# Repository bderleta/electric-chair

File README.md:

# Electric Chair

AVR Parallel Programmer

## Overview

This is an application of AVRxDB32 MCU with MCP2221A USB-UART/USB-I2C interface chip, implementing parallel programming protocol for ATmega32 and 
other MCUs with similar programming interface. 12V programming voltage is generated onboard by MAX632-based converter.

Firmware stub for AVR128DB32 is available at https://github.com/bderleta/electric-chair-firmware, probably it can be built for other chips from
AVRxDB32 family. The MCP2221A is running at its stock settings and no reconfiguration is necessary, though adjustment of power requirement limit is 
recommended.

## Known flaws of first revision
- Significant USB inrush current (can be adjusted by lowering C2 value, but...)
- Converter input ripple of about 100mV (still testing)
- "12V" and "HVRST" leds are consuming majority of converter's output :)

## Changes coming in second revision

- MAX662-based converter
- XTAL1 line connected to dedicated waveform output of AVR
- PROGRAM button connected to the CCL input in order to enable debouncing using CCL filters
- Elimination of 20-pin socket, instead DIP-40 and DIP-28 ZIF sockets will be placed

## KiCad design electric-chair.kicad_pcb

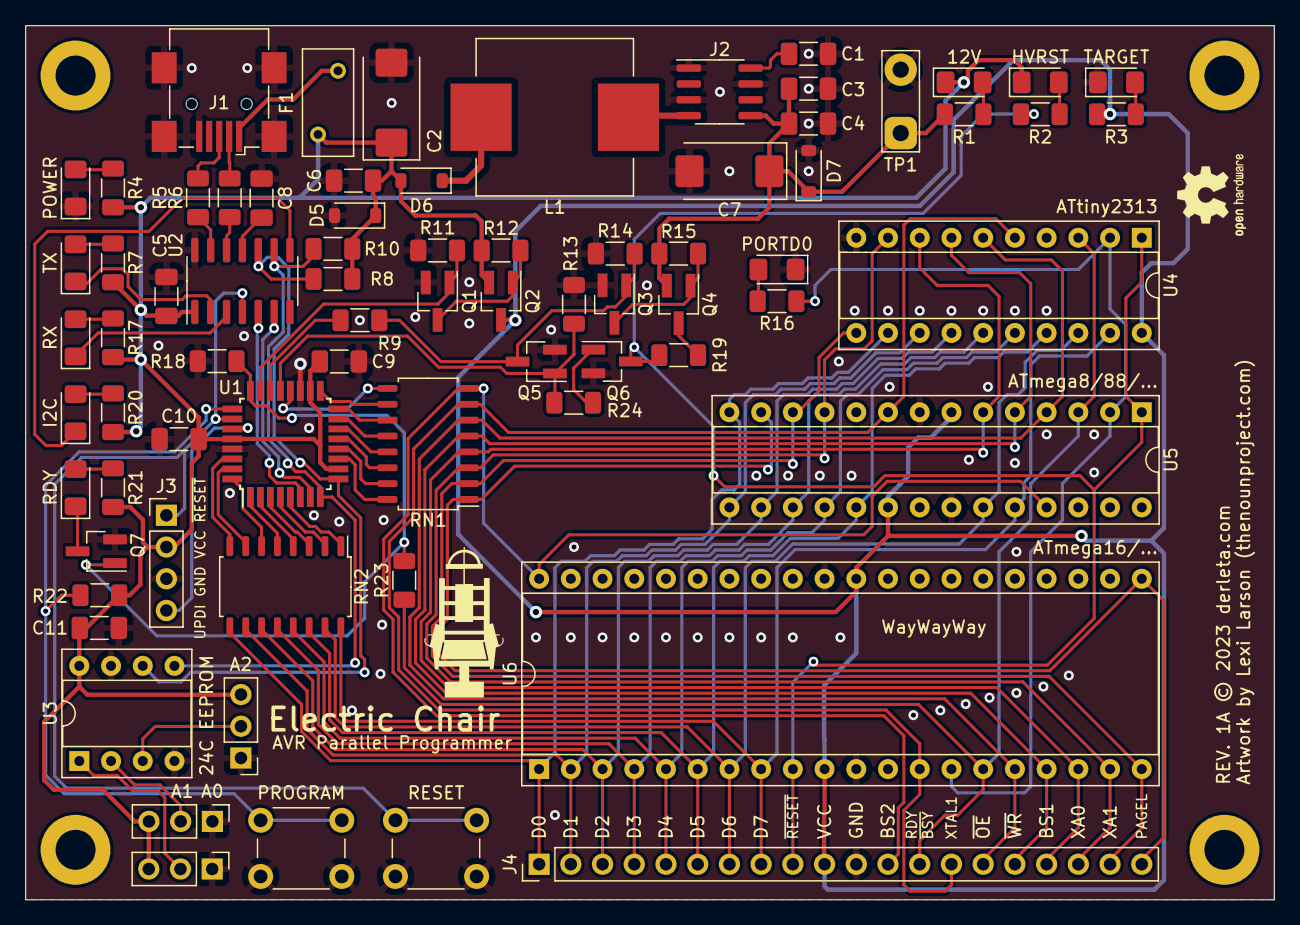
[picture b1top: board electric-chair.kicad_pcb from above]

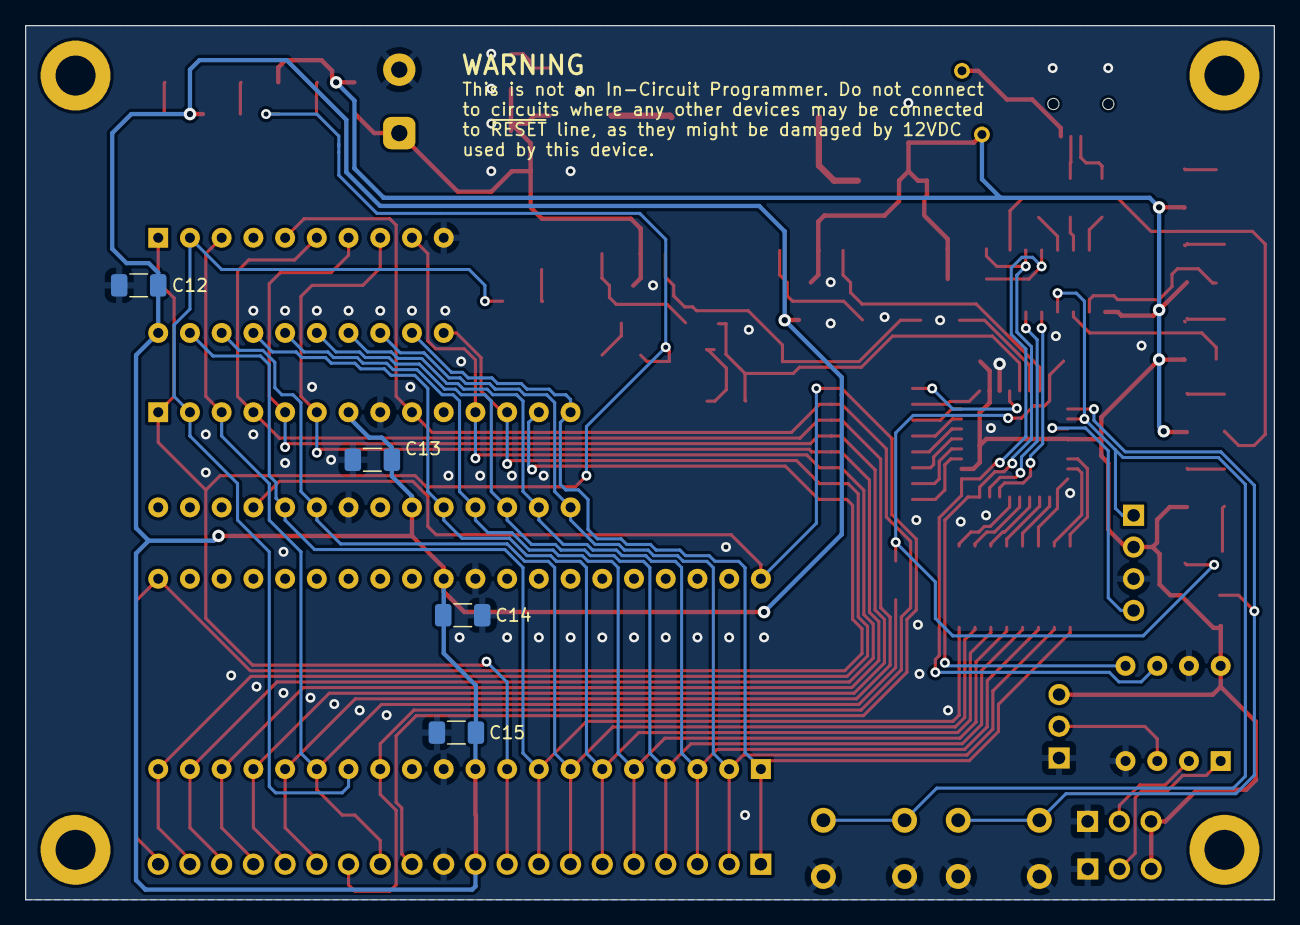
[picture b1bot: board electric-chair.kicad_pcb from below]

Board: 2 copper layers, 100.0 x 70.0 mm, 82 parts (4 on the bottom side), 80 nets.

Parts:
C1: 100p; C_1206_3216Metric_Pad1.33x1.80mm_HandSolder
C2: 4u7; CP_EIA-7343-31_Kemet-D_Pad2.25x2.55mm_HandSolder
C3, C5, C8, C10, C11, C12, C13, C14, C15: 100n; C_1206_3216Metric_Pad1.33x1.80mm_HandSolder
C4: 10u; C_1206_3216Metric_Pad1.33x1.80mm_HandSolder
C6: 1u; C_1206_3216Metric_Pad1.33x1.80mm_HandSolder
C7: 47u; CP_EIA-7343-31_Kemet-D_Pad2.25x2.55mm_HandSolder
C9: 10n; C_1206_3216Metric_Pad1.33x1.80mm_HandSolder
D1: 12V; LED_1206_3216Metric_Pad1.42x1.75mm_HandSolder
D2: HVRST; LED_1206_3216Metric_Pad1.42x1.75mm_HandSolder
D3: TARGET; LED_1206_3216Metric_Pad1.42x1.75mm_HandSolder
D4: POWER; LED_1206_3216Metric_Pad1.42x1.75mm_HandSolder
D5: 5V6; D_SOD-123
D6: STPS0520Z; D_SOD-123
D7: 13V; D_SOD-123
D8: TX; LED_1206_3216Metric_Pad1.42x1.75mm_HandSolder
D9: PORTD0; LED_1206_3216Metric_Pad1.42x1.75mm_HandSolder
D10: RX; LED_1206_3216Metric_Pad1.42x1.75mm_HandSolder
D11: I2C; LED_1206_3216Metric_Pad1.42x1.75mm_HandSolder
D12: RDY; LED_1206_3216Metric_Pad1.42x1.75mm_HandSolder
F1: R60-010; Fuse_BelFuse_0ZRE0005FF_L8.3mm_W3.8mm
H1, H2, H3, H4: MountingHole; MountingHole_3.2mm_M3_DIN965_Pad
J1: USB_B_Mini; USB_Mini-B_Wuerth_65100516121_Horizontal
J2: MAX632ACSA+; SOIC-8_3.9x4.9mm_P1.27mm
J3: SELFPROG; PinHeader_1x04_P2.54mm_Vertical
J4: DATA; PinHeader_1x20_P2.54mm_Vertical
JP1: A0; PinHeader_1x03_P2.54mm_Vertical
JP2: A1; PinHeader_1x03_P2.54mm_Vertical
JP3: A2; PinHeader_1x03_P2.54mm_Vertical
L1: 150uH; L_Wuerth_WE-PD-Typ-LS_Handsoldering
Q1, Q5, Q7: DMN2310U-7; SOT-23_Handsoldering
Q2: FDN302P; SOT-23_Handsoldering
Q3, Q6: IRFML8244TRPBF; SOT-23_Handsoldering
Q4: NTR0202PL; SOT-23_Handsoldering
R1, R2, R3, R4, R7, R17, R20, R21: 1-2k; R_1206_3216Metric_Pad1.30x1.75mm_HandSolder
R5, R6: 0; R_1206_3216Metric_Pad1.30x1.75mm_HandSolder
R8, R10: 2k7; R_1206_3216Metric_Pad1.30x1.75mm_HandSolder
R9: 1k (330?); R_1206_3216Metric_Pad1.30x1.75mm_HandSolder
R11, R12, R13, R14, R15, R22: 10k; R_1206_3216Metric_Pad1.30x1.75mm_HandSolder
R16: 330; R_1206_3216Metric_Pad1.30x1.75mm_HandSolder
R18: 100k - 1M; R_1206_3216Metric_Pad1.30x1.75mm_HandSolder
R19: 0 - 120 (75); R_1206_3216Metric_Pad1.30x1.75mm_HandSolder
R23: 1k; R_1206_3216Metric_Pad1.30x1.75mm_HandSolder
R24: 100 (75); R_1206_3216Metric_Pad1.30x1.75mm_HandSolder
RN1, RN2: R_Pack08; SOIC-16_4.55x10.3mm_P1.27mm
SW1: PROGRAM; SW_PUSH_6mm
SW2: RESET; SW_PUSH_6mm
TP1: 12V_TestPoint; TestPoint_2Pads_Pitch5.08mm_Drill1.3mm
U1: AVR32DB28x-xSO; TQFP-32_7x7mm_P0.8mm
U2: MCP2221AxP; SOIC-14_3.9x8.7mm_P1.27mm
U3: 24LC1025; DIP-8_W7.62mm_Socket
U4: ATtiny2313-20P; DIP-20_W7.62mm_Socket
U5: ATmega8A-P; DIP-28_W7.62mm_Socket
U6: ATmega32-16P; DIP-40_W15.24mm_Socket

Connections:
5V_EN: Q1.1 (G), R11.2, U1.23 (PF3)
12V_EN: R9.2, U1.22 (PF2)
+12V: C3.1, C4.1, C7.1, D7.1 (K), J2.5, Q4.2 (S), R1.2, R15.2, TP1.1
/COMP: C1.1, J2.8
/DD0: RN2.8 (R8.1), U1.30 (XTALHF1/PA0)
/DD1: RN2.7 (R7.1), U1.31 (XTALHF2/PA1)
/DD2: RN2.6 (R6.1), U1.32 (PA2)
/DD3: RN2.5 (R5.1), U1.1 (PA3)
/DD4: RN2.4 (R4.1), U1.2 (PA4)
/DD5: RN2.3 (R3.1), U1.3 (PA5)
/DD6: RN2.2 (R2.1), U1.4 (PA6)
/DD7: RN2.1 (R1.1), U1.5 (PA7)
/LX: J2.4, L1.1
/LXI: D6.1 (K), L1.2
/POWER_LED_A: D4.2 (A), R4.1
/Peripherals/I2C_LED_A: D11.2 (A), R20.1
/Peripherals/I2C_LED_C: D11.1 (K), U2.8 (GP3)
/Peripherals/RX_LED_A: D8.2 (A), R7.1
/Peripherals/RX_LED_C: D8.1 (K), U2.2 (GP0)
/Peripherals/TX_LED_A: D10.2 (A), R17.1
/Peripherals/TX_LED_C: D10.1 (K), U2.3 (GP1)
/Peripherals/VCCUSB: F1.2, J1.1 (VBUS)
/TARGET_LED_A: D3.2 (A), R3.1
/Target/PD0_LED_A: D9.2 (A), R16.1
/UPDI: J3.4, U1.27 (UPDI)
BS1: J4.17, RN1.4 (R4.1), U4.8 (PD4), U5.6 (PD4), U6.18 (PD4)
BS2: J4.12, RN1.8 (R8.1), U5.25 (PC2), U6.40 (PA0)
D0: J4.1, RN2.9 (R8.2), U4.12 (PB0), U5.14 (PB0), U6.1 (PB0)
D1: J4.2, RN2.10 (R7.2), U4.13 (PB1), U5.15 (PB1), U6.2 (PB1)
D2: J4.3, RN2.11 (R6.2), U4.14 (PB2), U5.16 (PB2), U6.3 (PB2)
D3: J4.4, RN2.12 (R5.2), U4.15 (PB3), U5.17 (PB3), U6.4 (PB3)
D4: J4.5, RN2.13 (R4.2), U4.16 (PB4), U5.18 (PB4), U6.5 (PB4)
D5: J4.6, RN2.14 (R3.2), U4.17 (PB5), U5.19 (PB5), U6.6 (PB5)
D6: J4.7, RN2.15 (R2.2), U4.18 (PB6), U5.23 (PC0), U6.7 (PB6)
D7: J4.8, RN2.16 (R1.2), U4.19 (PB7), U5.24 (PC1), U6.8 (PB7)
GND: C1.2, C2.2, C3.2, C4.2, C5.1, C6.1, C7.2, C8.1, C9.1, C10.1, C11.2, C12.2, C13.1, C14.1, C15.1, D3.1 (K), D4.1 (K), D5.2 (A), D7.2 (A), D9.1 (K), J1.5 (GND), J1.6 (Shield), J2.1, J2.3, J2.7, J3.3, J4.11, JP1.1 (A), JP2.1 (A), JP3.1 (A), Q1.2 (S), Q3.2 (S), Q5.2 (S), Q6.2 (S), Q7.2 (S), R11.1, R13.1, R14.1, R18.2, SW1.2 (B), SW2.2 (B), TP1.2, U1.19 (AGND), U1.29 (GND), U2.14 (VSS), U3.4 (GND), U3.7 (WP), U4.10 (GND), U5.8 (GND), U5.22 (AGND), U6.11 (GND), U6.31 (GND)
unnamed: D1.2 (A), R1.1
unnamed: D2.2 (A), R2.1
unnamed: D12.2 (A), R21.1
unnamed: D12.1 (K), Q7.3 (D)
unnamed: J1.3 (D+), R5.1
unnamed: J1.2 (D-), R6.2
unnamed: JP1.2 (C), U3.1 (A0)
unnamed: JP2.2 (C), U3.2 (A1)
unnamed: JP3.2 (C), U3.3 (A2)
unnamed: Q1.3 (D), Q2.1 (G), R12.1
unnamed: Q3.3 (D), Q4.1 (G), R15.1
unnamed: Q3.1 (G), Q5.3 (D), R9.1, R14.2
unnamed: Q4.3 (D), R19.2
unnamed: Q6.1 (G), R24.2
unnamed: RN1.16 (R1.2), U1.11 (PD1)
unnamed: RN1.15 (R2.2), U1.12 (PD2)
unnamed: RN1.14 (R3.2), U1.13 (PD3)
unnamed: RN1.13 (R4.2), U1.14 (PD4)
unnamed: RN1.12 (R5.2), U1.15 (PD5)
unnamed: RN1.11 (R6.2), U1.16 (PD6)
unnamed: RN1.10 (R7.2), U1.17 (VREFA/PD7)
unnamed: RN1.9 (R8.2), U1.20 (XTAL32K1/PF0)
unnamed: R5.2, U2.13 (D+)
unnamed: R6.1, U2.12 (D-)
unnamed: C8.2, U2.11 (VUSB)
PAGEL: J4.20, RN1.1 (R1.1), U5.13 (PD7), U6.21 (PD7)
PD0: R16.2, U4.2 (PD0), U5.2 (PD0), U6.14 (PD0)
PROGRAM: R22.1, SW1.1 (A)
RDY_LED: Q7.1 (G), R18.1, R23.2, U1.24 (PF4)
RDY/~BSY: J4.13, R23.1, U4.3 (PD1), U5.3 (PD1), U6.15 (PD1)
RXD1: U1.7 (PC1), U2.6 (UTx)
SCL: R8.1, U1.9 (PC3), U2.10 (SCL), U3.6 (SCL)
SDA: R10.1, U1.8 (PC2), U2.9 (SDA), U3.5 (SDA)
TRESET: Q5.1 (G), R13.2, R24.1, U1.21 (XTAL32K2/PF1)
TXD1: U1.6 (PC0), U2.5 (URx)
VCC: C2.1, C5.2, C6.2, C9.2, C10.2, C11.1, D1.1 (K), D2.1 (K), D5.1 (K), D6.2 (A), F1.1, J3.2, JP1.3 (B), JP2.3 (B), JP3.3 (B), Q2.2 (S), R4.2, R7.2, R8.2, R10.2, R12.2, R17.2, R20.2, R21.2, R22.2, U1.10 (VDDIO2), U1.18 (AVDD), U1.28 (VDD), U2.1 (VDD), U3.8 (VCC)
VDD: C12.1, C13.2, C14.2, C15.2, J4.10, Q2.3 (D), R3.2, U4.20 (VCC), U5.7 (VCC), U5.20 (AVCC), U6.10 (VCC), U6.30 (AVCC)
VRESET: J4.9, Q6.3 (D), R2.2, R19.1, U4.1 (PA2/~RESET), U5.1 (PC6/~RESET), U6.9 (~RESET)
XA0: J4.18, RN1.3 (R3.1), U4.9 (PD5), U5.11 (PD5), U6.19 (PD5)
XA1: J4.19, RN1.2 (R2.1), U4.11 (PD6), U5.12 (PD6), U6.20 (PD6)
XTAL1: J4.14, RN1.7 (R7.1), U4.5 (PA0/XTAL1), U5.9 (PB6/XTAL1), U6.13 (XTAL1)
~OE: J4.15, RN1.6 (R6.1), U4.6 (PD2), U5.4 (PD2), U6.16 (PD2)
~RESET: J3.1, SW2.1 (A), U1.26 (~RESET/PF6), U2.4 (~RST)
~WR: J4.16, RN1.5 (R5.1), U4.7 (PD3), U5.5 (PD3), U6.17 (PD3)

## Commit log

2023-11-13 images
2023-11-13 Docs
2023-11-16 Value fixes

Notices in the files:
electric-chair.kicad_pcb:
REV. 1A © 2023 derleta.com
